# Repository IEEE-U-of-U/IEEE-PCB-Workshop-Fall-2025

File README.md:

# IEEE PCB Workshop Fall 2025

## Introduction
Welcome to the IEEE PCB Workshop Series for Fall 2025 at the University of Utah!

## General Information

We will be hosting this workshop over 8-9 weeks this semester, currently scheduled for **Wednesdays at 4:10 PM to 5:30 PM** beginning September 3rd and ending November 12th (see tentative schedule below). Sessions may go overtime to 6:00 PM depending on the topic covered. To help alleviate these longer sessions, food may be provided (tentatively planned). All planned dates are shown below.

The workshops will be held in **WEB L102** unless otherwise specified.

We will be presenting a design for a *USB-C Breadboard Power Supply* and all participants are invited to participate in designing, manufacturing, and assembling their own PCBs, which they will be able to keep at the end.

__Workshop Goals__

- Introduction to PCB design
- Introduction to ECAD software (Altium, KiCAD)
- Introduction to Schematic Layout
- Introduction to PCB Layout
- Basics of PCB Manufacturing
- Introduction to Soldering
- Introduction to Verification and Debugging

## ECAD Software

### ALTIUM Designer (Highly Recommended)
Altium is the software that is going to be desmonstrated during the workshop and will be the easiest to follow along. All resources provided will be natively supported in Altium Designer.

If you plan to use Altium, please complete the instructions for registering and installing Altium on a personal machine. This allows us to immediately begin our workshop sessions without troubleshooting.

Altium License Instructions:
https://docs.google.com/document/d/1AU2HPewD7sdPoBuVvdMO27dwBopvW5h48ppQYsgPDJ0/edit?usp=sharing

### KiCAD

Please install KiCAD if you are not using Altium. While we do support this program, as KiCAD can import Altium files, we will be focusing on Altium Designer.

KiCAD Official Page:
https://www.kicad.org/

## Schedule

| DATE   | SESSION Title | LINK |
|--------|---------------|------|
| Sep 3  | Introduction to Schematics | [Week 01](https://github.com/IEEE-U-of-U/IEEE-PCB-Workshop-Fall-2025/tree/main/Week01) |
| Sep 10 | Schematics and Components | [Week 02](https://github.com/IEEE-U-of-U/IEEE-PCB-Workshop-Fall-2025/tree/main/Week02) |
| Sep 17 | Introduction to PCB Layout | [Week 03](https://github.com/IEEE-U-of-U/IEEE-PCB-Workshop-Fall-2025/tree/main/Week03) |
| Sep 24 | Footprints and PCB Layout | [Week 04](https://github.com/IEEE-U-of-U/IEEE-PCB-Workshop-Fall-2025/tree/main/Week04) |
| Oct 1  | Open Work Session | [Week 05](https://github.com/IEEE-U-of-U/IEEE-PCB-Workshop-Fall-2025/tree/main/Week05) |
| Oct 22 | Soldering Week 1 | [Week 06](https://github.com/IEEE-U-of-U/IEEE-PCB-Workshop-Fall-2025/tree/main/Week06) |
| Oct 29 | Soldering Week 2 | [Week 07](https://github.com/IEEE-U-of-U/IEEE-PCB-Workshop-Fall-2025/tree/main/Week07) |
| Nov 5  | Soldering Week 3 | [Week 08](https://github.com/IEEE-U-of-U/IEEE-PCB-Workshop-Fall-2025/tree/main/Week08) |
| Nov 12 | Final Notes and Next Steps | [Week 09](https://github.com/IEEE-U-of-U/IEEE-PCB-Workshop-Fall-2025/tree/main/Week09) |

While it is recommended to attend all sessions, we will provide the design and workshop files through a GitHub repository. To stay up to date, please be sure to follow along to not fall behind.

## Contact Info

- Questions may be routed to the IEEE email: ieee.studentbranch.uofu@gmail.com
- Updates are also posted on the IEEE / ECE discord: https://discord.gg/TMjhuDCCfy

## Sign-Up Flyer

Sign-Up Form:
[Form](https://forms.gle/3xZnF7SPggJ7AQWy9)

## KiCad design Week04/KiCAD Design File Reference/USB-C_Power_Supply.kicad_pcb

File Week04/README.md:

# WEEK 04 RESOURCES

## Summary

Sept 24th, 2025

- Review of Libraries
- Introduction to Gerber Files
- Creating Schematic/PCB Footprints
- Generation of Gerber Files
- Additional PCB Design Guidance
- Free work time / Individual Questions

## Tasks

- Continue working on your own PCB layout. We will continue to work on layout next week, however, please make as much progress as possible if you have the time.
- If you don't finish layout by the final submission in October, you can still continue the soldering portion of the workshop with a reference board.

## Recording

Recording posted to YouTube: https://www.youtube.com/watch?v=sjpjHsPAj8o

## Files
### Altium Design File Reference.zip
Altium Files for the Week04 Workshop. Includes all necessary files to follow along in the session.

### Altium Workshop Week 04 - Footprints and PCB Layout.pdf
Workshop introduction presentation on PCB Layout. Basic information regarding PCBs and some of the best practices related to layout.

### KiCAD Design File Reference.zip
KiCAD Files and Library for the Week04 Workshop. Includes all necessary files to follow along for most of the session.

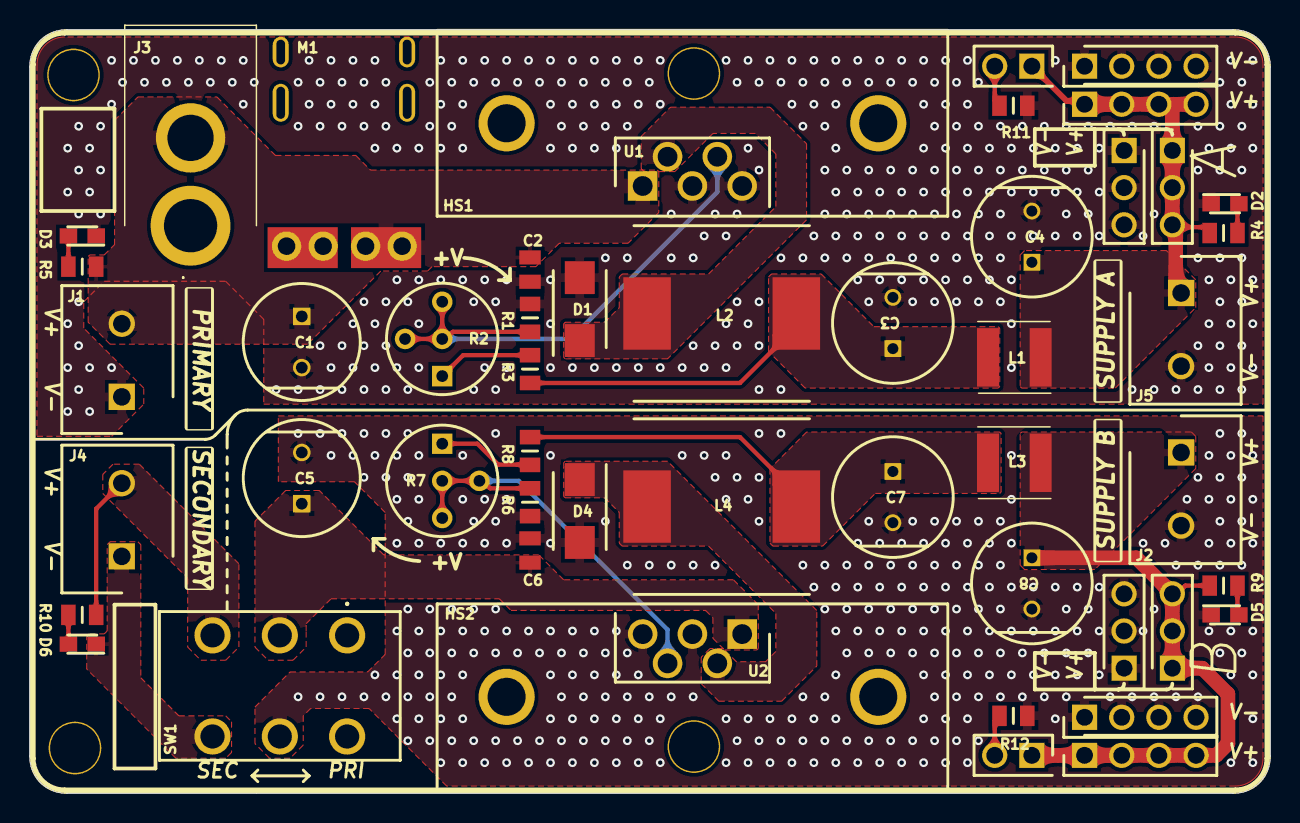
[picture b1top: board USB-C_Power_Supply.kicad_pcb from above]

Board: 2 copper layers, 84.8 x 52.2 mm, 51 parts (0 on the bottom side), 22 nets.

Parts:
C1, C5: ESL227M035AG8AA; CAPTH8.00X18.00-3.50
C2, C6: 100n; CAP0805
C3, C4, C7, C8: REF0816471M025K; CAPTH8.00X16.00-3.50
D1, D4: SS510B; DO-214AC (SMA)
D2, D3, D5, D6: LED; LEDM2012X80N
H1, H3, H5, H7: Header; Header_1X4
H2, H4, H6, H8: Header; Header_1X3
HS1, HS2: 637-10ABPE; 63710ABPE
J1, J2, J4, J5: 691137710002; SHDR2W70P0X500_1X2_1000X750X1160P
J3: PJ-037AH; PJ037AH
J6, J7: 90120-0762; Header_1X2
L1, L3: NRS5030T4R7MMGJ; IND (4.9mmx4.9mm)
L2, L4: SRR1210-151M; INDPM120120X1000N-D
M1: USB-PD; USB_C-PD
R1, R3, R6, R8: 1k; RESC0805
R2, R7: 10k; 3339P1103LF - Modified
R4, R5, R9, R10, R11, R12: 3.3k; RESC0805
SW1: GF-126-0305; GF1260305
U1, U2: LM2576WT; TO-220-5

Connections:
+VCC_A: C4.1, H1.1, H1.2, H1.3, H1.4, H2.1, H2.2, H2.3, J2.1, J6.1, L1.2, R4.1
+VCC_B: C8.1, H5.1, H5.2, H5.3, H5.4, H6.1, H6.2, H6.3, J5.1, J7.1, L3.2, R9.1
GND_A: C1.2, C2.2, C3.2, C4.2, D1.2, D2.1, D3.1, H3.1, H3.2, H3.3, H3.4, H4.1, H4.2, H4.3, J1.1, J2.2, J3.1, M1.2, R1.2, R11.2, SW1.6, U1.3, U1.5
GND_B: C5.2, C6.2, C7.2, C8.2, D4.2, D5.1, H7.1, H7.2, H7.3, H7.4, H8.1, H8.2, H8.3, J5.2, R6.2, R12.2, SW1.5, U2.3, U2.5
NetC3_1: C3.1, L1.1, L2.2, R3.1
NetC7_1: C7.1, L3.1, L4.2, R8.1
NetD1_1: D1.1, L2.1, U1.2
NetD2_2: D2.2, R4.2
NetD3_2: D3.2, R5.2
NetD4_1: D4.1, L4.1, U2.2
NetD5_2: D5.2, R9.2
NetD6_2: D6.2, R10.2
NetJ6_2: J6.2, R11.1
NetJ7_2: J7.2, R12.1
NetR1_1: R1.1, R2.2, R2.3, U1.4
NetR2_1: R2.1, R3.2
NetR6_1: R6.1, R7.2, R7.3, U2.4
NetR7_1: R7.1, R8.2
SEC_GND: D6.1, J4.1, SW1.4
V_IN_A: C1.1, C2.1, J1.2, J3.2, M1.1, R5.1, SW1.1, U1.1
V_IN_B: C5.1, C6.1, SW1.2, U2.1
V_IN_SEC: J4.2, R10.1, SW1.3

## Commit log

2025-08-31 Initial Week01 Commit
2025-09-02 Updated Week01 Resources
2025-09-03 Added Master Reference Files
2025-09-10 Added Week02 Materials
2025-09-12 Updated Week02 YT Link
2025-09-17 Added Week03 Resources
2025-09-24 Week04 Resources
2025-09-24 File name correction
2025-10-01 Week05 Resources
2025-10-01 Rules Files
2025-10-29 Week06 Resources
